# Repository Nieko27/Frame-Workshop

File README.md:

> ⚠️ This is an unofficial 3rd-party project with no association to Valve.

# What is Frame Workshop?
Frame Workshop is intended to be an open-source bundle of different hardware peripherals built around (but not always exclusive to) the Steam Frame. The idea is to leverage the Steam Frames' modularity and general openness to create a collection of open-source hardware projects that the community can provide feedback on, expand upon, or even take and turn into something entirely new, creating a feedback loop that adds to an ever-expanding ecosystem for the Steam Frame. All source files, from schematics to STLs, will be included, allowing every aspect of each project to be modified and produced to anyone’s preferences. 

## Hardware
Below is a list of all currently in development hardware projects, including a brief overview and notes on changes made to the most recent revision.

### Frame Facetracker

| 🛑R&D | hw: EV2 | 
| -------- | ------- |

The Frame face tracker is pretty self-explanatory: it is a module that uses a camera for face tracking in social experiences like VRChat. There are 2 versions planned: one built with the steam frame in mind, using its expansion ports, and another that plugs into the back USB port of the frame and uses an ESP32 to run the camera.

>Headset-Agnostic Version EV2

<br>

Link to the facetracker files:
[Here](https://github.com/Nieko27/FrameWork/tree/main/KICAD%20Projects/Primis_FaceTracker)

### Versipellis (General Purpose Dongle)

| 🟠WIP | hw: EV2 | 
| -------- | ------- |

Versipellis is a dongle utilising an nRF52833 intended as a general-purpose dongle for communicating with any Frame-based hardware, whether it be controllers or trackers. It will be programmable by the end user for whatever they intend to use it for. There will be two versions: one utilising no parts smaller than a 0603 package, making it easy to hand-assemble, and another using much smaller parts that, while smaller, will require assembly by a service like JLCPCB.

>Hand-assemblable EV1

<br>

Link to Versipellis' files:
[Here](https://github.com/Nieko27/FrameWork/tree/main/KICAD%20Projects/Primis_Versipellis)

### VeriMini

| 🛑R&D | hw: EV1 | 
| -------- | ------- |

Link to VeriMini files:
[Here](https://github.com/Nieko27/Frame-Workshop/tree/main/KICAD%20Projects/Primis_VeriMini)

### Locus (Tracker)

| 🛑R&D | hw: EV2 | 
| -------- | ------- |

Locus is intended to be a tracker like Vive or Tundra, but without reliance on lighthouse base stations. Since the Steam Frame isn’t limited to base station vision, trackers being used with it shouldn’t be either. Similar to Versipellis, Locus will also use an nRF52833 along with an LSM6DSV16X IMU. The idea is that it will track similarly to a slime tracker, but also use the Steam Frame’s optical tracking to address the drift problem of EMF trackers. 

Link to Locus' files:
[Here](https://github.com/Nieko27/FrameWork/tree/main/KICAD%20Projects/Primis_Locus)

## Project Status Indicator

| 🔵STATUS | hw: EV1 | fw: v0.0.0 | sw: v0.0.0 |
| -------- | ------- | ---------- | ---------- |

The above status indicator is listed for each Frame Workshop accessory. It shows overall progress as well as the latest upstreamed hardware, firmware, and/or software versions. Here's what each status means:

**🔴R&D**: This accessory is experimental. The latest hardware revision is either untested, incomplete, or broken. Capabilities are unproven. Form factor and design requirements may change entirely. Intended for use by hardware contributors.

**🟠WIP**: The current hardware revision has been tested and is fully capable of meeting established design requirements. Firmware and/or software are in active development. Future hardware revisions may still follow if oversights or improvements are discovered. Intended for use by software contributors.

**🟡PRE**: This accessory has reached a pre-release stage. Hardware is finalized. Firmware and software meets functional requirements but may still be buggy or unintuitive. Documentation is not yet up to release standards. Considered usable for tinkerers and early adopters.

**🟢REL**: This accessory is considered released and fully functional both in software and hardware. Documentation is available to assist with ordering components, assembly, and usage. Software and firmware QOL updates may still follow but will be distributed through user friendly means.

### Future Projects
* USB Hub
* Index speaker mod kit

## Accessories and CAD
While 3D models for each electronics project are in the 3D models folder, I also plan to make several other CAD files available for accessories that don't require electronics. Things like lens caps, headset stands, battery or IO expansion holders, etc.
<br>
https://github.com/Nieko27/Frame-Workshop/tree/main/3D%20Models/Accessories

## Project Goals

* Keep costs to the users as low as possible. You've already spent over a $1000 on the headset itself, so it would be nice not to have to spend another $1000 customizing it to your liking. How this would be achieved is by everything being open and nothing being sold, for example I’m working on a face tracker that takes advantage of the PCIe port on the Frame, the idea is when its done instead of me having to handle production, shipping and all the joys of selling a project I give the source files out with a tutorial on how to order it yourself from a company like JLCPCB. Now, obviously, this still won't be free to the end user, but it will be much cheaper than if I were to sell it. For example, I have made the first prototype of the face-tracker, and in small quantities (5 to be exact), it cost me $25 per board. Compare that to something like the old Vive face trackers, which I think were closer to $100, and you save a nice bit of money. 

* Give the end user total control over the hardware. Don't like how I've done something? Fire up Blender or KiCad and change it yourself to fit whatever need you have in mind. I know not everyone will be able to do this, as it requires familiarity with the software, but it gives people the ability to do so. Obviously, with this in mind, I want to make the experience for everyone as smooth as possible out of the box, so I will be listening to feedback as much as possible to achieve that. 

* Create a feedback loop. I have all this under a CERN-OHL-S-2.0 license, which (as far as I understand) means you can do anything you want with anything in the repo, including selling it for profit, but you must open-source anything you do under the same license. This way it keeps everything open to the community, and every addition helps grow the ecosystem around the Steam Frame. 

## Note
A forewarning, I am very new to electronics design in general. I apologize in advance for any really baffling design decisions. I hope to learn from these projects and will keep them updated as I learn more. Thank you for your patience.

## Ideas
A few ideas for possible mods for the Frame have already been thrown around. If you have an idea for a mod, whether it's a full module or as simple as a 3D-printable counterweight, feel free to open a pull request under the enhancement tag. You may also feel free to email me at nieko972@gmail.com.

### Find me on
* Twitter; https://x.com/Merlinr271
* Bluesky; https://bsky.app/profile/merlin271.bsky.social

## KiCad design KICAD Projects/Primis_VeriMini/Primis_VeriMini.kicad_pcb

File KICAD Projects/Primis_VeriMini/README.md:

### Status

| 🛑R&D | hw: EV1 | 
| -------- | ------- |

> This accessory is experimental. The latest hardware revision is either untested, incomplete, or broken. Capabilities are unproven. Form factor and design requirements may change entirely. Intended for use by hardware contributors.

# VERI-MINI
The general purpose dongle for the Steam Frame but smaller.

### Schematics

### PCB

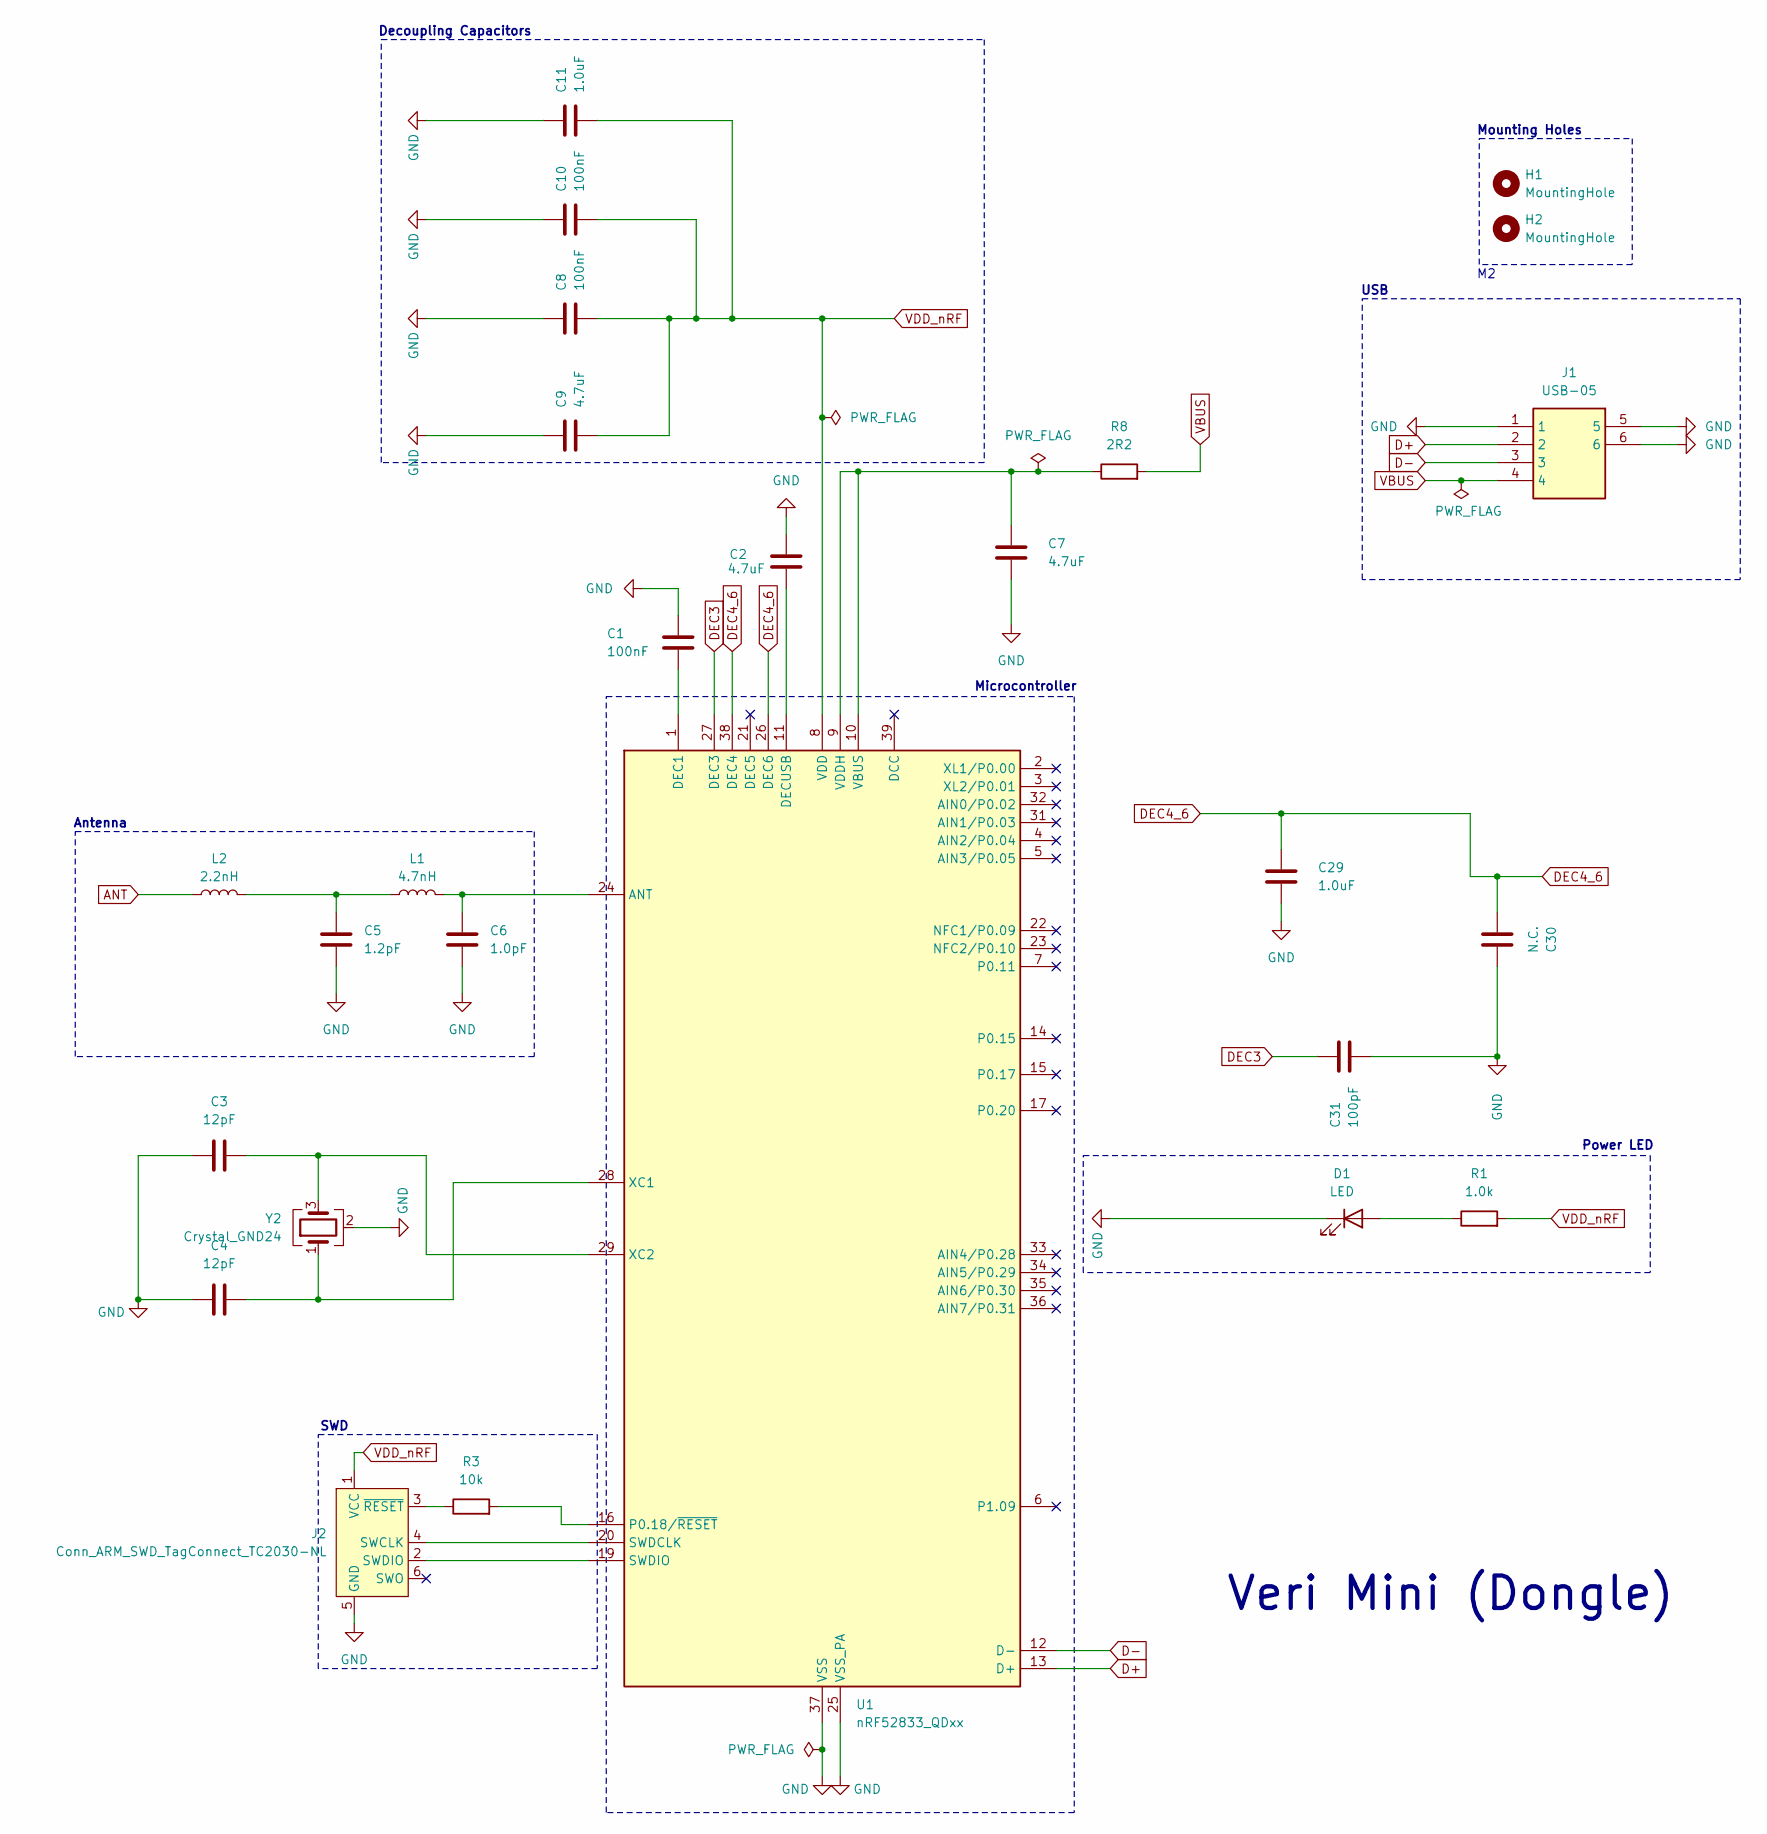
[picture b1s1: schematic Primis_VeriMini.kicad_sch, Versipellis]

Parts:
C1, C8, C10: 100nF; C_0402_1005Metric
C2, C7, C9: 4.7uF; C_0603_1608Metric
C3, C4: 12pF; C_0402_1005Metric
C5: 1.2pF; C_0402_1005Metric
C6: 1.0pF; C_0402_1005Metric
C11, C29: 1.0uF; C_0402_1005Metric
C30: N.C.; C_0402_1005Metric
C31: 100pF; C_0402_1005Metric
D1: LED; LED_0603_1608Metric
H1, H2: MountingHole; MountingHole_2.2mm_M2
J1: USB-05; USB05; Manufacturer_Part_Number USB-05
J2: Conn_ARM_SWD_TagConnect_TC2030-NL; Tag-Connect_TC2030-IDC-NL_2x03_P1.27mm_Vertical
L1: 4.7nH; L_0402_1005Metric
L2: 2.2nH; L_0402_1005Metric
R1: 1.0k; R_0402_1005Metric
R3: 10k; R_0603_1608Metric
R8: 2R2; R_0603_1608Metric
U1: nRF52833_QDxx; QFN-40-1EP_5x5mm_P0.4mm_EP3.6x3.6mm
Y2: Crystal_GND24; Crystal_SMD_Abracon_ABM8G-4Pin_3.2x2.5mm

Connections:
ANT: L2.1
D+: J1.2, U1.13 (D+)
D-: J1.3, U1.12 (D-)
DEC3: C31.1, U1.27 (DEC3)
DEC4_6: C29.1, C30.2, U1.26 (DEC6), U1.38 (DEC4)
GND: C1.1, C2.2, C3.1, C4.1, C5.1, C6.1, C7.2, C8.1, C9.2, C10.1, C11.2, C29.2, C30.1, C31.2, D1.1 (K), J1.1, J1.5, J1.6, J2.5 (GND), U1.25 (VSS_PA), U1.37 (VSS), U1.41 (VSS), Y2.2 (G), Y2.4 (G)
unnamed: C5.2, L1.1, L2.2
unnamed: D1.2 (A), R1.1
unnamed: J2.4 (SWCLK), U1.20 (SWDCLK)
unnamed: J2.2 (SWDIO), U1.19 (SWDIO)
unnamed: J2.3 (~RESET), R3.1
unnamed: C6.2, L1.2, U1.24 (ANT)
unnamed: C1.2, U1.1 (DEC1)
unnamed: C2.1, U1.11 (DECUSB)
unnamed: R3.2, U1.16 (P0.18/~RESET)
unnamed: C7.1, R8.1, U1.9 (VDDH), U1.10 (VBUS)
unnamed: C4.2, U1.28 (XC1), Y2.1
unnamed: C3.2, U1.29 (XC2), Y2.3
VBUS: J1.4, R8.2
VDD_nRF: C8.2, C9.1, C10.2, C11.1, J2.1 (VCC), R1.2, U1.8 (VDD), U1.18 (VDD), U1.30 (VDD), U1.40 (VDD)

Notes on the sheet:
Mounting Holes
Decoupling Capacitors
Microcontroller
Veri Mini (Dongle)
SWD
Antenna
Power LED
USB

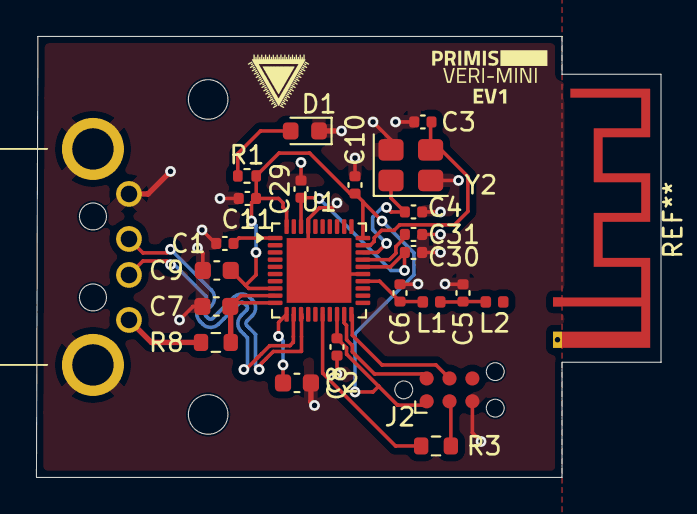
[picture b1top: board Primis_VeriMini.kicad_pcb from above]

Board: 2 copper layers, 34.7 x 24.5 mm, 26 parts (0 on the bottom side), 19 nets.

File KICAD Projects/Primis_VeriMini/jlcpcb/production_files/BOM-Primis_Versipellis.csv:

Comment,Designator,Footprint,LCSC,Quantity
1.2pF,C5,C_0603_1608Metric,,1
2R2,R8,R_0805_2012Metric,,1
1.0pF,C6,C_0603_1608Metric,,1
12pF,C4,C_0603_1608Metric,,1
4.7uF,C2,C_0603_1608Metric,,1
USB-05,J1,USB05,,1
WS2812B-2020,D3,LED_WS2812B-2020_PLCC4_2.0x2.0mm,,1
4.7uF,C9,C_0603_1608Metric,,1
nRF52833_QDxx,U1,QFN-40-1EP_5x5mm_P0.4mm_EP3.6x3.6mm,,1
100nF,C8,C_0603_1608Metric,,1
12pF,C3,C_0603_1608Metric,,1
100pF,C31,C_0603_1608Metric,,1
1.0k,R1,R_0603_1608Metric,,1
4.7uF,C7,C_0603_1608Metric,,1
LED,D1,LED_0603_1608Metric,,1
N.C.,C30,C_0603_1608Metric,,1
1.0uF,C29,C_0603_1608Metric,,1
1.0uF,C11,C_0603_1608Metric,,1
Crystal_GND24,Y2,Crystal_SMD_Abracon_ABM8G-4Pin_3.2x2.5mm,,1
100nF,C10,C_0603_1608Metric,,1
2.2nH,L2,L_0603_1608Metric,,1
10k,R3,R_0603_1608Metric,,1
4.7nH,L1,L_0603_1608Metric,,1
100nF,C1,C_0603_1608Metric,,1
100nF,C12,C_0603_1608Metric,,1

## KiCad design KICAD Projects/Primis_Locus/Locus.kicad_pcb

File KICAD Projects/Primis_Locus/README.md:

### Status

| 🛑R&D | hw: EV2 | 
| -------- | ------- |

> This accessory is experimental. The latest hardware revision is either untested, incomplete, or broken. Capabilities are unproven. Form factor and design requirements may change entirely. Intended for use by hardware contributors.

## Current Isseus
Currently the SDA line is getting pulled 0.02v while running the slime firmware, if I halt the NRF52833 it jumps up to the expected 1.8v. Currently working on figuring out why this happens.

### Schematics

### PCB

### EV1

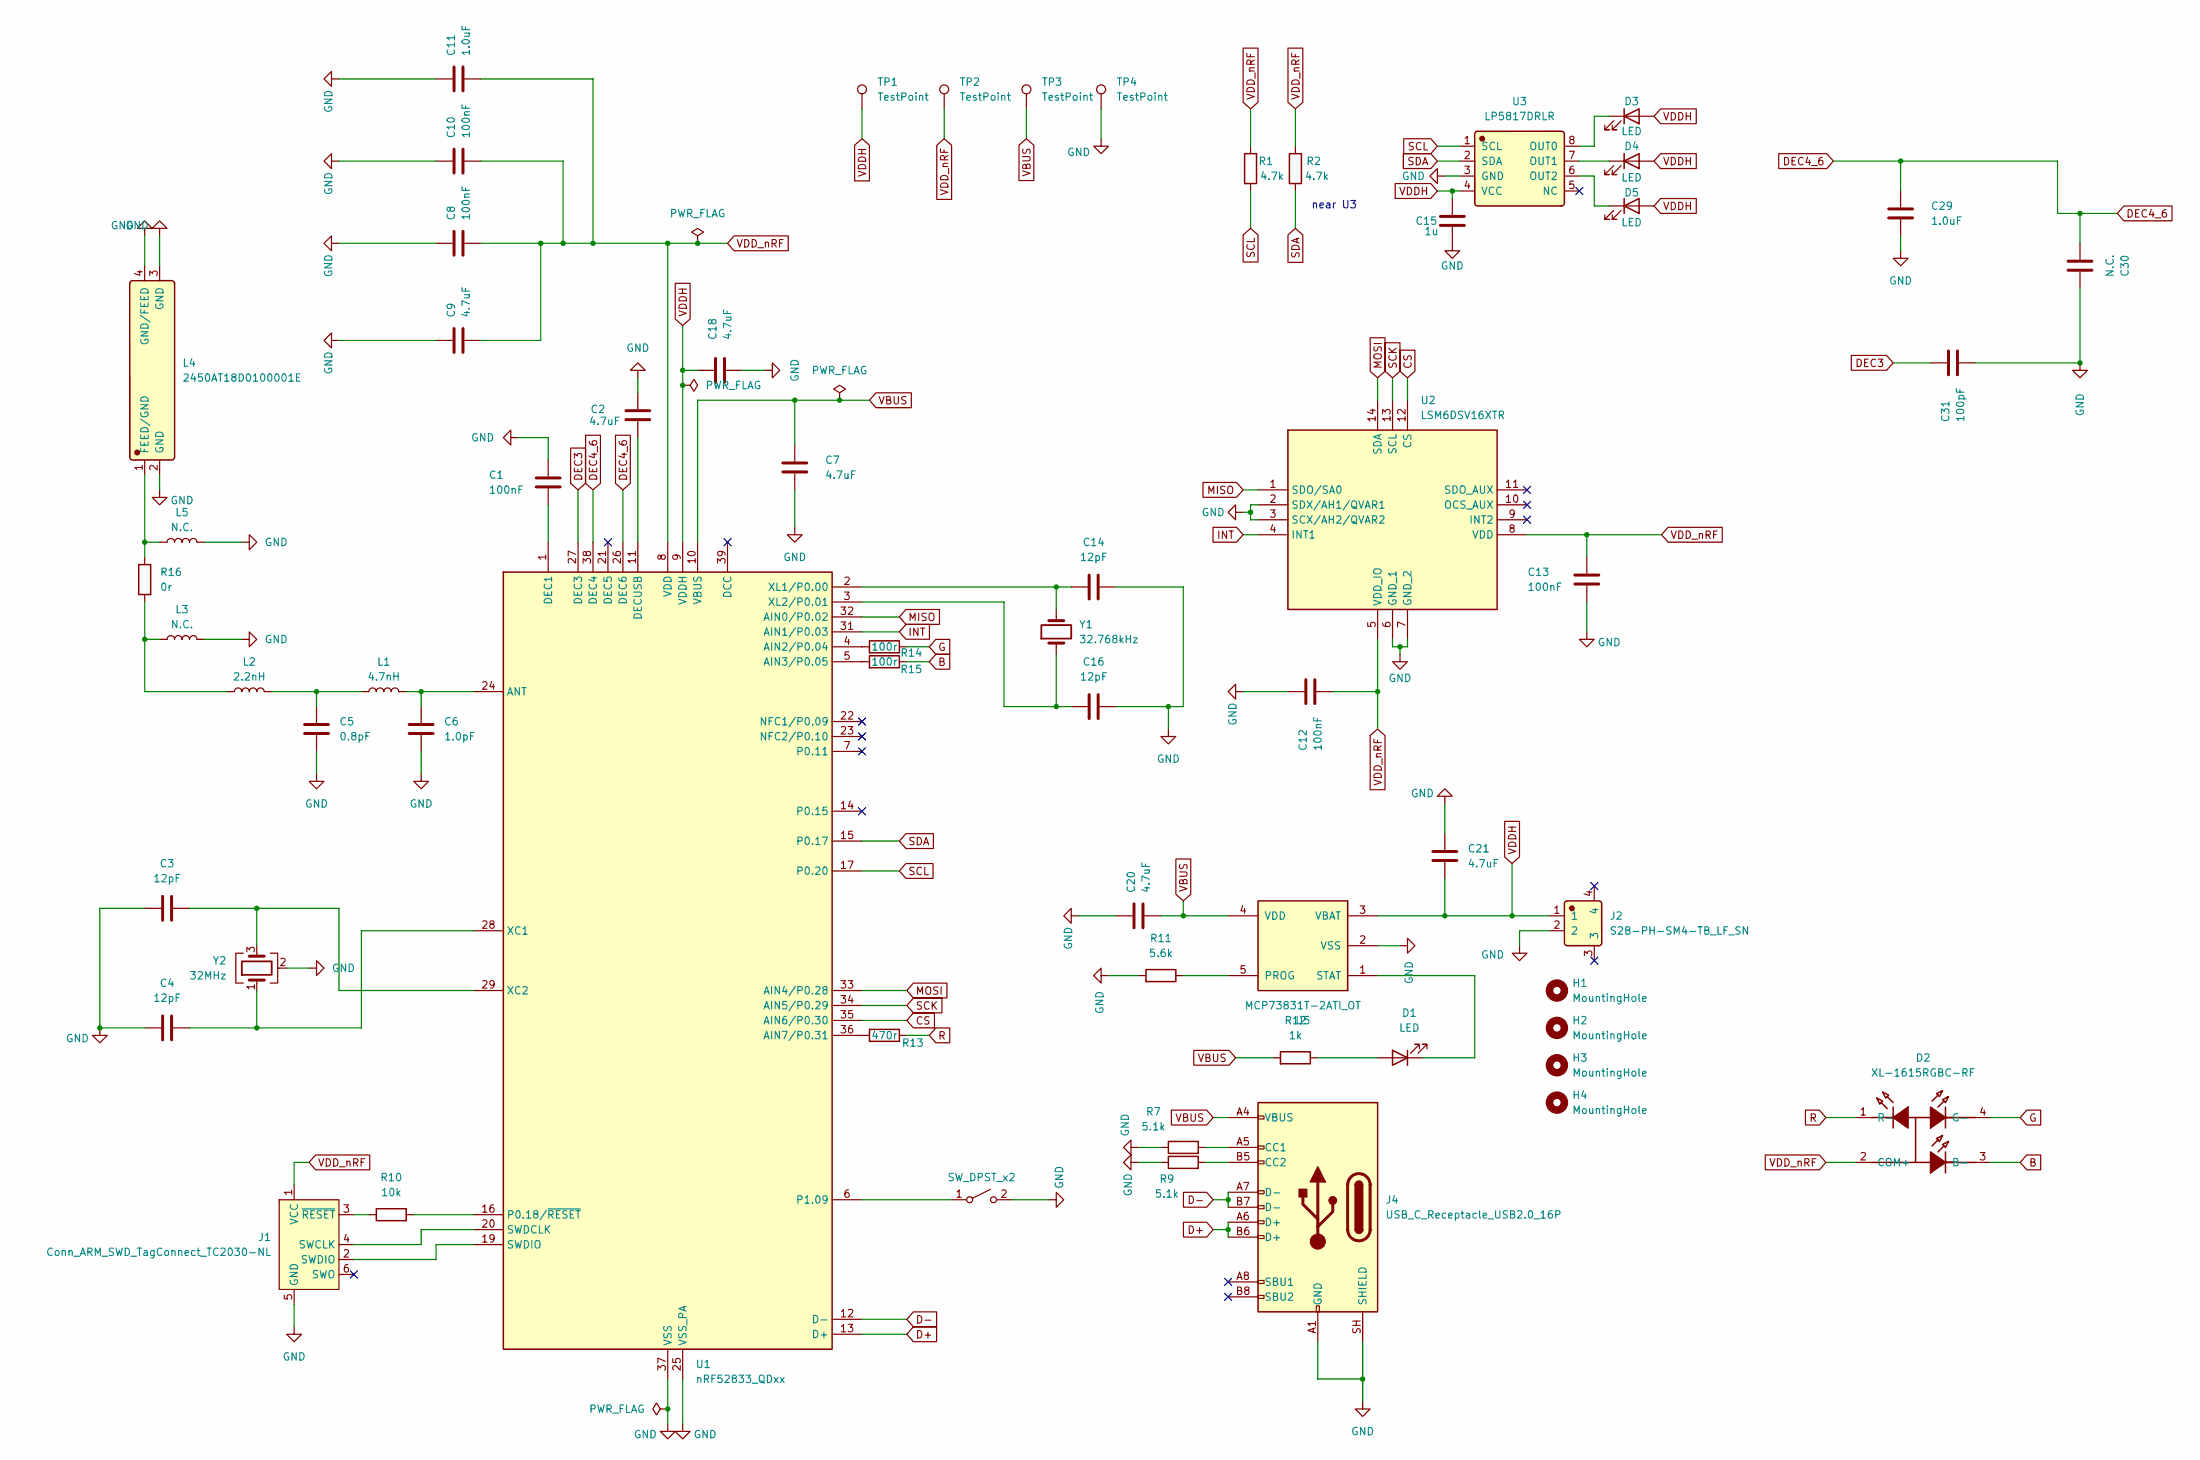
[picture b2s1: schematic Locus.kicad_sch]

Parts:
C1, C8, C10, C12, C13: 100nF; C_0402_1005Metric
C2, C7, C9, C18, C20, C21: 4.7uF; C_0603_1608Metric
C3, C4, C14, C16: 12pF; C_0402_1005Metric
C5: 0.8pF; C_0402_1005Metric
C6: 1.0pF; C_0402_1005Metric
C11, C29: 1.0uF; C_0402_1005Metric
C15: 1u; C_0402_1005Metric
C30: N.C.; C_0402_1005Metric
C31: 100pF; C_0402_1005Metric
D1: LED; LED_0603_1608Metric
D2: XL-1615RGBC-RF; Manufacturer Part XL-1615RGBC-RF; LCSC C965840
D3, D4, D5: LED; LED_0805_2012Metric
H1, H2, H3, H4: MountingHole; MountingHole_2.7mm_M2.5
J1: Conn_ARM_SWD_TagConnect_TC2030-NL; Tag-Connect_TC2030-IDC-NL_2x03_P1.27mm_Vertical
J2: S2B-PH-SM4-TB_LF_SN; Manufacturer Part S2B-PH-SM4-TB(LF)(SN); LCSC C295747
J4: USB_C_Receptacle_USB2.0_16P; USB_C_Receptacle_HRO_TYPE-C-31-M-12
L1: 4.7nH; L_0402_1005Metric
L2: 2.2nH; L_0402_1005Metric
L3, L5: N.C.; L_0402_1005Metric
L4: 2450AT18D0100001E; Manufacturer Part 2450AT18D0100001E; LCSC C7450310
R1, R2: 4.7k; R_0402_1005Metric
R7, R9: 5.1k; R_0402_1005Metric
R10: 10k; R_0402_1005Metric
R11: 5.6k; R_0402_1005Metric
R12: 1k; R_0402_1005Metric
R13: 470r; R_0402_1005Metric
R14, R15: 100r; R_0402_1005Metric
R16: 0r; R_0402_1005Metric
SW1: SW_DPST_x2; SH-1806SA-A3DW-04
TP1, TP2, TP3, TP4: TestPoint; TestPoint_Pad_1.0x1.0mm
U1: nRF52833_QDxx; QFN-40-1EP_5x5mm_P0.4mm_EP3.6x3.6mm
U2: LSM6DSV16XTR; LSM6DSV16BXTR; Manufacturer_Part_Number LSM6DSV16XTR; Mouser Part Number 511-LSM6DSV16XTR
U3: LP5817DRLR; Manufacturer Part LP5817DRLR; LCSC C47262829
U5: MCP73831T-2ATI_OT; Manufacturer Part MCP73831T-2ATI/OT; LCSC C14879
Y1: 32.768kHz; SC-20S32_768kHz20PPM9pF
Y2: 32MHz; NX2016SA-32MHZ-STD-CZS-5

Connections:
B: D2.3 (B-), R15.1
CS: U1.35 (AIN6/P0.30), U2.12 (CS)
D+: J4.A6 (D+), J4.B6 (D+), U1.13 (D+)
D-: J4.A7 (D-), J4.B7 (D-), U1.12 (D-)
DEC3: C31.1, U1.27 (DEC3)
DEC4_6: C29.1, C30.2, U1.26 (DEC6), U1.38 (DEC4)
G: D2.4 (G-), R14.1
GND: C1.1, C2.2, C3.1, C4.1, C5.1, C6.1, C7.2, C8.1, C9.2, C10.1, C11.2, C12.1, C13.2, C14.1, C15.2, C16.2, C18.2, C20.2, C21.1, C29.2, C30.1, C31.2, J1.5 (GND), J2.2, J4.A1 (GND), J4.A12 (GND), J4.B1 (GND), J4.B12 (GND), J4.SH (SHIELD), L3.2, L4.2 (GND), L4.3 (GND), L4.4 (GND/FEED), L5.2, R7.1, R9.1, R11.2, SW1.2 (B), TP4.1 (1_1), U1.25 (VSS_PA), U1.37 (VSS), U1.41 (VSS), U2.2 (SDX/AH1/QVAR1), U2.3 (SCX/AH2/QVAR2), U2.6 (GND_1), U2.7 (GND_2), U3.3 (GND), U5.2 (VSS), Y2.2 (G), Y2.4 (G)
INT: U1.31 (AIN1/P0.03), U2.4 (INT1)
MISO: U1.32 (AIN0/P0.02), U2.1 (SDO/SA0)
MOSI: U1.33 (AIN4/P0.28), U2.14 (SDA)
unnamed: C5.2, L1.1, L2.2
unnamed: D1.2 (A), R12.1
unnamed: D1.1 (K), U5.1 (STAT)
unnamed: D3.1 (K), U3.8 (OUT0)
unnamed: D4.1 (K), U3.7 (OUT1)
unnamed: D5.1 (K), U3.6 (OUT2)
unnamed: J1.4 (SWCLK), U1.20 (SWDCLK)
unnamed: J1.2 (SWDIO), U1.19 (SWDIO)
unnamed: J1.3 (~RESET), R10.1
unnamed: J4.A5 (CC1), R7.2
unnamed: J4.B5 (CC2), R9.2
unnamed: L2.1, L3.1, R16.2
unnamed: L4.1 (FEED/GND), L5.1, R16.1
unnamed: SW1.1 (A), U1.6 (P1.09)
unnamed: R14.2, U1.4 (AIN2/P0.04)
unnamed: R15.2, U1.5 (AIN3/P0.05)
unnamed: R13.2, U1.36 (AIN7/P0.31)
unnamed: C6.2, L1.2, U1.24 (ANT)
unnamed: C1.2, U1.1 (DEC1)
unnamed: C2.1, U1.11 (DECUSB)
unnamed: R10.2, U1.16 (P0.18/~RESET)
unnamed: C4.2, U1.28 (XC1), Y2.1
unnamed: C3.2, U1.29 (XC2), Y2.3
unnamed: C14.2, U1.2 (XL1/P0.00), Y1.2
unnamed: C16.1, U1.3 (XL2/P0.01), Y1.1
unnamed: R11.1, U5.5 (PROG)
R: D2.1 (R-), R13.1
SCK: U1.34 (AIN5/P0.29), U2.13 (SCL)
SCL: R1.2, U1.17 (P0.20), U3.1 (SCL)
SDA: R2.2, U1.15 (P0.17), U3.2 (SDA)
VBUS: C7.1, C20.1, J4.A4 (VBUS), J4.A9 (VBUS), J4.B4 (VBUS), J4.B9 (VBUS), R12.2, TP3.1 (1_1), U1.10 (VBUS), U5.4 (VDD)
VDDH: C15.1, C18.1, C21.2, D3.2 (A), D4.2 (A), D5.2 (A), J2.1, TP1.1 (1_1), U1.9 (VDDH), U3.4 (VCC), U5.3 (VBAT)
VDD_nRF: C8.2, C9.1, C10.2, C11.1, C12.2, C13.1, D2.2 (COM+), J1.1 (VCC), R1.1, R2.1, TP2.1 (1_1), U1.8 (VDD), U1.18 (VDD), U1.30 (VDD), U1.40 (VDD), U2.5 (VDD_IO), U2.8 (VDD)

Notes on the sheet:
near U3

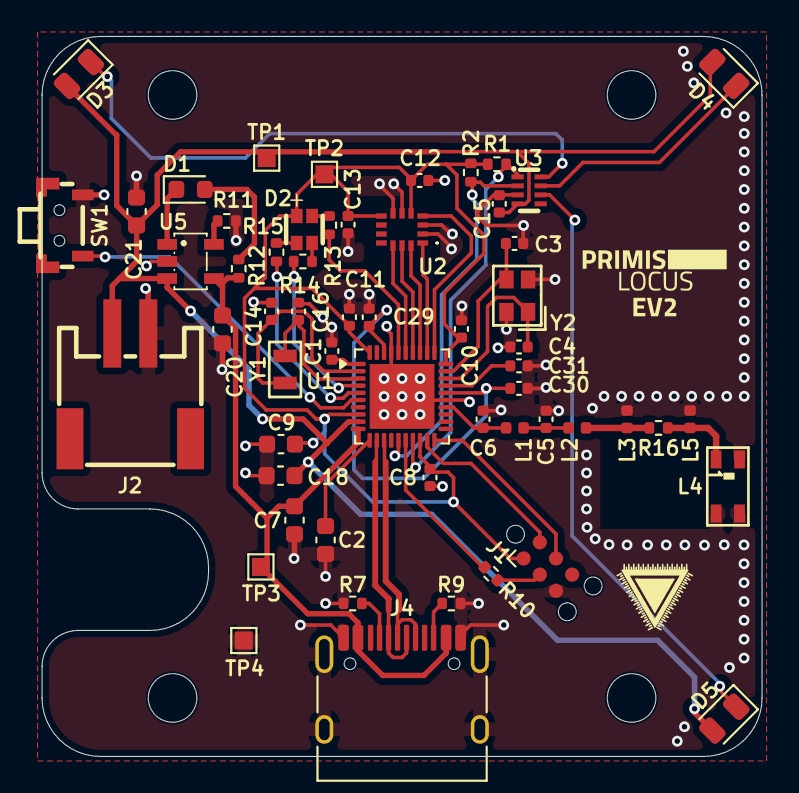
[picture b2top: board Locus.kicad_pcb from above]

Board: 4 copper layers, 40.0 x 40.0 mm, 61 parts (0 on the bottom side), 44 nets.

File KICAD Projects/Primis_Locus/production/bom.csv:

Designator,Footprint,Quantity,Value,LCSC Part #
"C1, C10, C12, C13, C8",0402,5,100nF,
"C11, C29",0402,2,1.0uF,
"C14, C16, C3, C4",0402,4,12pF,
C17,0603,1,2.2uF,
"C18, C2, C20, C21, C7, C9",0603,6,4.7uF,
"C30, L3, L5",0402,3,N.C.,
C31,0402,1,100pF,
C5,0402,1,0.8pF,
C6,0402,1,1.0pF,
D1,0603,1,LED,
D2,XL-1615RGBC-RF,1,XL-1615RGBC-RF,C965840
J2,S2B-PH-SM4-TB_LF_SN,1,S2B-PH-SM4-TB_LF_SN,C295747
J4,USB_C_Receptacle_HRO_TYPE-C-31-M-12,1,USB_C_Receptacle_USB2.0_16P,
L1,0402,1,4.7nH,
L2,0402,1,2.2nH,
L4,2450AT18D0100001E,1,2450AT18D0100001E,C7450310
"R1, R2, R4",0402,3,4.7k,
R10,0402,1,10k,
R11,0402,1,5.6k,
R12,0402,1,1k,
R13,0402,1,470r,
"R14, R15",0402,2,100r,
R16,0402,1,0r,
"R7, R9",0402,2,5.1k,
SW1,SH-1806SA-A3DW-04,1,SW_DPST_x2,C22383476
"TP1, TP2, TP3, TP4",TestPoint_Pad_1.0x1.0mm,4,TestPoint,
U1,QFN-40-1EP_5x5mm_P0.4mm_EP3.6x3.6mm,1,nRF52833_QDxx,
U2,LSM6DSV16BXTR,1,LSM6DSV16XTR,
U3,QMC6309,1,QMC6309,
U5,MCP73831T-2ATI_OT,1,MCP73831T-2ATI_OT,C14879
Y1,SC-20S32_768kHz20PPM9pF,1,32.768kHz,C97603
Y2,NX2016SA-32MHZ-STD-CZS-5,1,32MHz,C843260

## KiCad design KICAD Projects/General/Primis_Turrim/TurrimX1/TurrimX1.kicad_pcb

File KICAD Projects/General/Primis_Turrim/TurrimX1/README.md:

### WARNING
This has yet to be produced by me yet, I have not yet added the gerber files to this repo yet as I have no idea if it will work yet, order them at your own risk.
# Dongle Dock (1-Port)
Headset-agnostic face tracker. Can be used with Frame by using the USB-C port on the battery.

### Schematics

### PCB

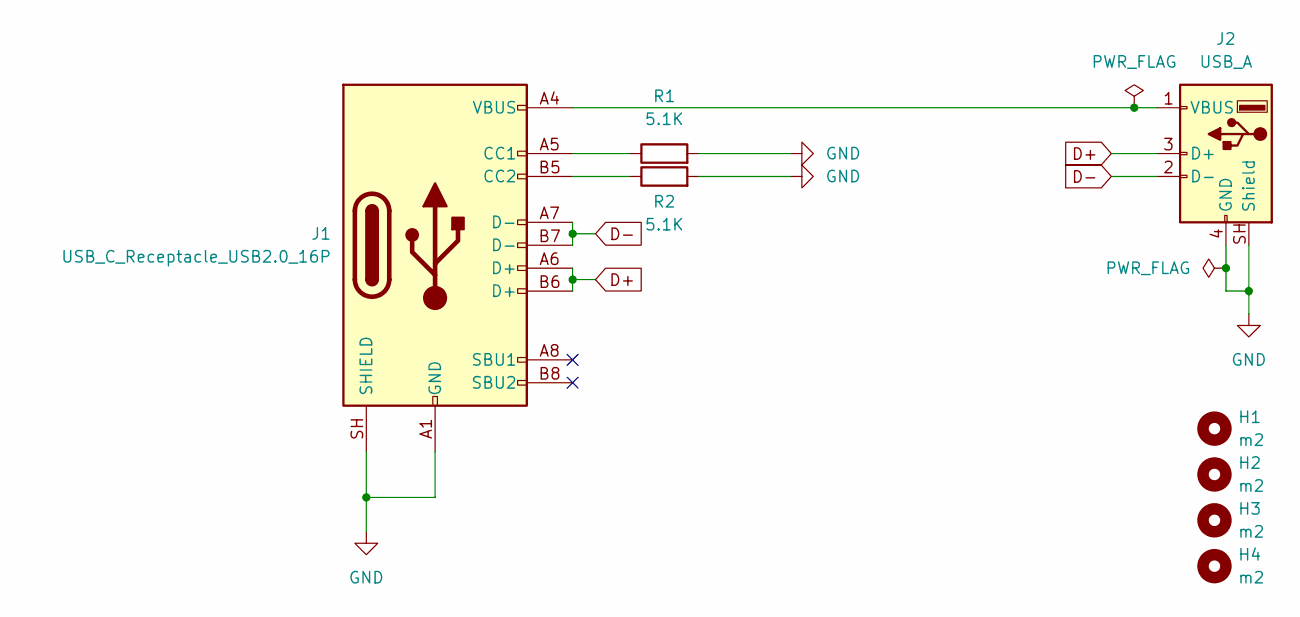
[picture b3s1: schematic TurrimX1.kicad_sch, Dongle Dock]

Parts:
H1, H2, H3, H4: m2; MountingHole_2.2mm_M2
J1: USB_C_Receptacle_USB2.0_16P; USB_C_Receptacle_HRO_TYPE-C-31-M-12
J2: USB_A; USB_A_Molex_105057_Vertical
R1, R2: 5.1K; R_0805_2012Metric

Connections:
D+: J1.A6 (D+), J1.B6 (D+), J2.3 (D+)
D-: J1.A7 (D-), J1.B7 (D-), J2.2 (D-)
GND: J1.A1 (GND), J1.A12 (GND), J1.B1 (GND), J1.B12 (GND), J1.SH (SHIELD), J2.4 (GND), J2.SH (Shield), R1.2, R2.2
unnamed: J1.A5 (CC1), R1.1
unnamed: J1.B5 (CC2), R2.1
unnamed: J1.A4 (VBUS), J1.A9 (VBUS), J1.B4 (VBUS), J1.B9 (VBUS), J2.1 (VBUS)

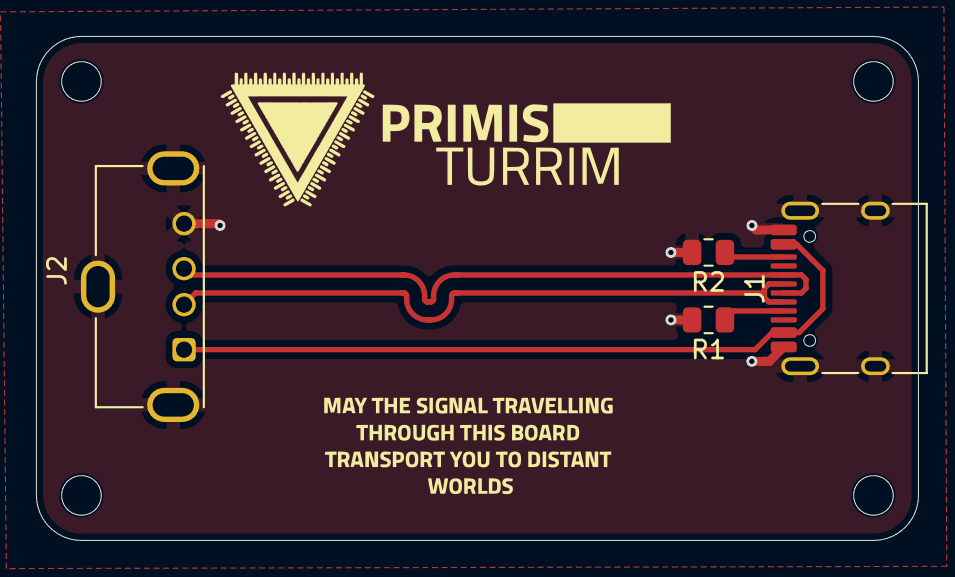
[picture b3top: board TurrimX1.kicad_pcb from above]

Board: 2 copper layers, 49.0 x 28.0 mm, 8 parts (0 on the bottom side), 6 nets.

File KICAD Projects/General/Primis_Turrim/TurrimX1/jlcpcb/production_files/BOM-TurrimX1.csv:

Comment,Designator,Footprint,LCSC,Quantity
5.1K,R2,R_0805_2012Metric,,1
5.1K,R1,R_0805_2012Metric,,1
USB_A,J2,USB_A_Molex_105057_Vertical,,1
USB_C_Receptacle_USB2.0_16P,J1,USB_C_Receptacle_HRO_TYPE-C-31-M-12,,1

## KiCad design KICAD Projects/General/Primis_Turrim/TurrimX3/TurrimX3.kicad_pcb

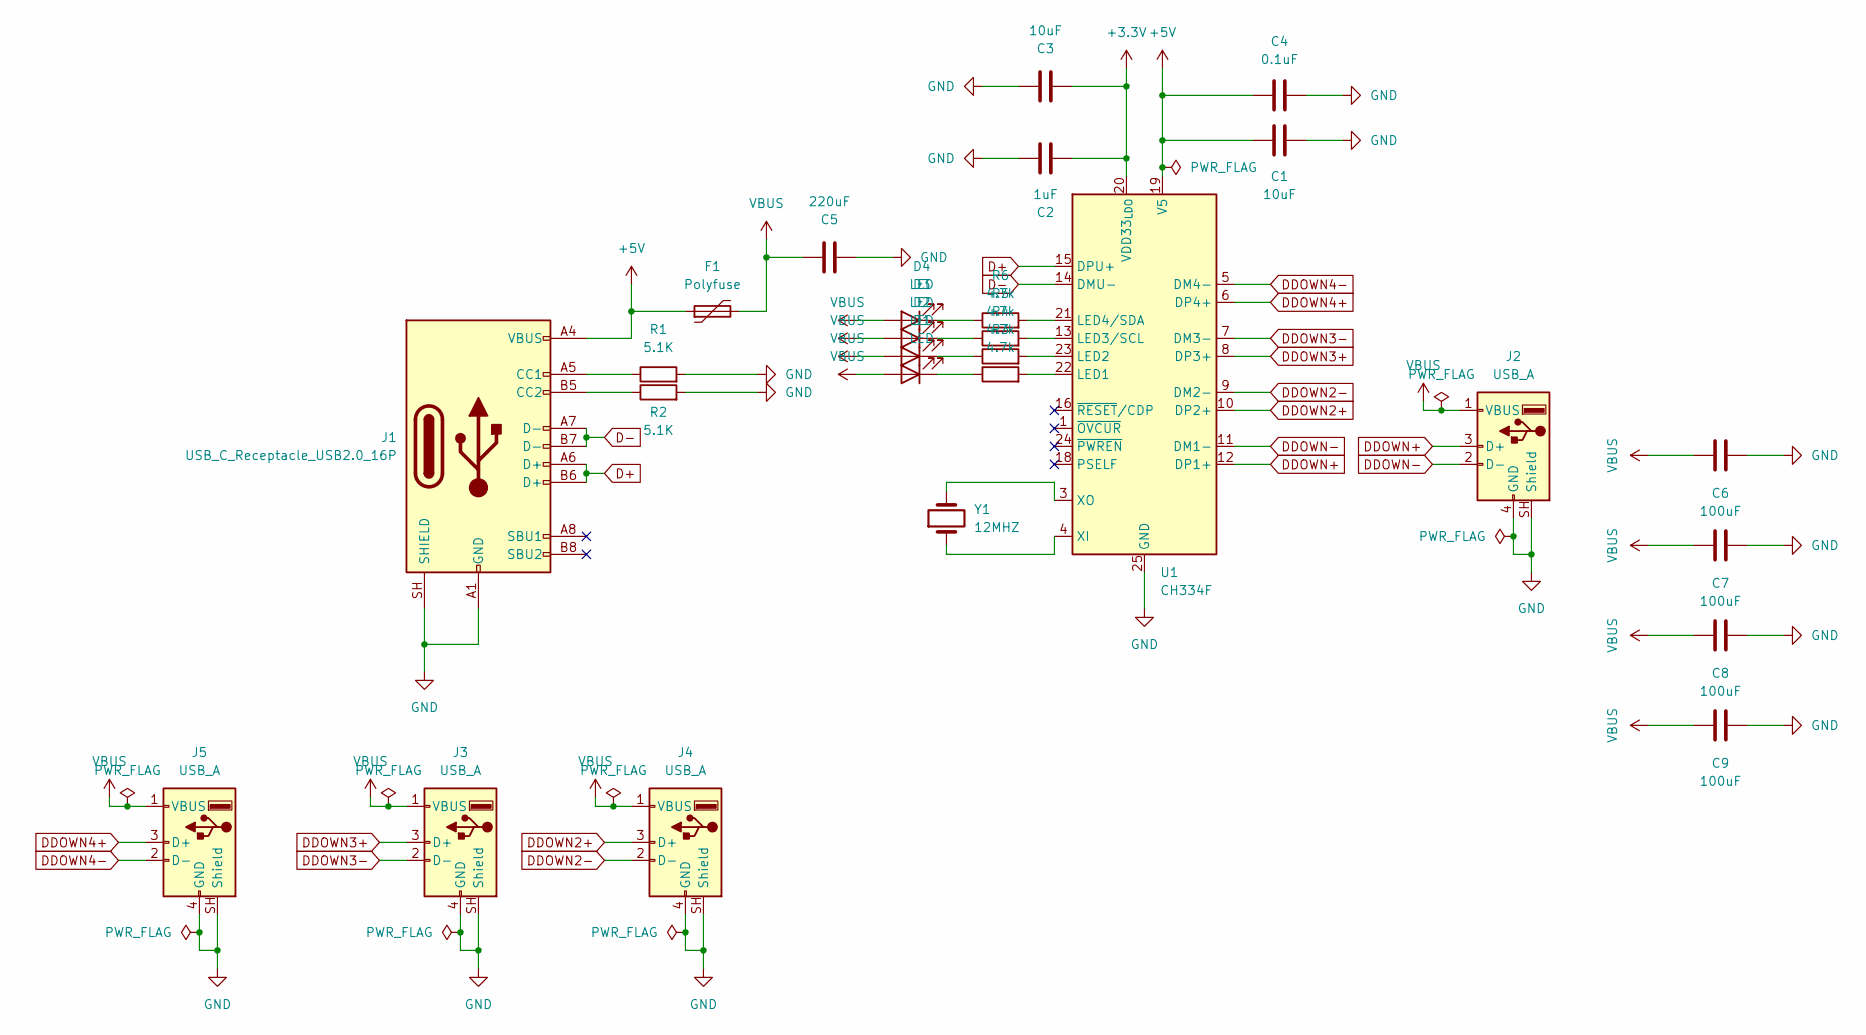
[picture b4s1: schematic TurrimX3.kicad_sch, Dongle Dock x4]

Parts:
C1, C3: 10uF; C_0805_2012Metric
C2: 1uF; C_0603_1608Metric
C4: 0.1uF; C_0603_1608Metric
C5: 220uF; C_0805_2012Metric
C6, C7, C8, C9: 100uF; C_0805_2012Metric
D1, D2, D3, D4: LED; LED_0603_1608Metric
F1: Polyfuse; Fuse_1206_3216Metric
J1: USB_C_Receptacle_USB2.0_16P; USB_C_Receptacle_HRO_TYPE-C-31-M-12
J2, J3, J4, J5: USB_A; USB_A_Molex_105057_Vertical
R1, R2: 5.1K; R_0805_2012Metric
R3, R4, R5, R6: 4.7k; R_0805_2012Metric
U1: CH334F; QFN-24-1EP_4x4mm_P0.5mm_EP2.7x2.7mm
Y1: 12MHZ; Crystal_SMD_2016-4Pin_2.0x1.6mm

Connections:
+3.3V: C2.1, C3.1, U1.20 (VDD33_{LDO})
+5V: C1.1, C4.1, F1.1, J1.A4 (VBUS), J1.A9 (VBUS), J1.B4 (VBUS), J1.B9 (VBUS), U1.19 (V5)
D+: J1.A6 (D+), J1.B6 (D+), U1.15 (DPU+)
D-: J1.A7 (D-), J1.B7 (D-), U1.14 (DMU-)
DDOWN2+: J4.3 (D+), U1.10 (DP2+)
DDOWN2-: J4.2 (D-), U1.9 (DM2-)
DDOWN3+: J3.3 (D+), U1.8 (DP3+)
DDOWN3-: J3.2 (D-), U1.7 (DM3-)
DDOWN4+: J5.3 (D+), U1.6 (DP4+)
DDOWN4-: J5.2 (D-), U1.5 (DM4-)
DDOWN+: J2.3 (D+), U1.12 (DP1+)
DDOWN-: J2.2 (D-), U1.11 (DM1-)
GND: C1.2, C2.2, C3.2, C4.2, C5.1, C6.2, C7.2, C8.2, C9.2, J1.A1 (GND), J1.A12 (GND), J1.B1 (GND), J1.B12 (GND), J1.SH (SHIELD), J2.4 (GND), J2.SH (Shield), J3.4 (GND), J3.SH (Shield), J4.4 (GND), J4.SH (Shield), J5.4 (GND), J5.SH (Shield), R1.2, R2.2, U1.25 (GND)
unnamed: D1.1 (K), R3.1
unnamed: D2.1 (K), R4.1
unnamed: D3.1 (K), R5.1
unnamed: D4.1 (K), R6.1
unnamed: J1.A5 (CC1), R1.1
unnamed: J1.B5 (CC2), R2.1
unnamed: R3.2, U1.22 (LED1)
unnamed: R4.2, U1.23 (LED2)
unnamed: R5.2, U1.13 (LED3/SCL)
unnamed: R6.2, U1.21 (LED4/SDA)
unnamed: U1.4 (XI), Y1.1
unnamed: U1.3 (XO), Y1.2
VBUS: C5.2, C6.1, C7.1, C8.1, C9.1, D1.2 (A), D2.2 (A), D3.2 (A), D4.2 (A), F1.2, J2.1 (VBUS), J3.1 (VBUS), J4.1 (VBUS), J5.1 (VBUS)

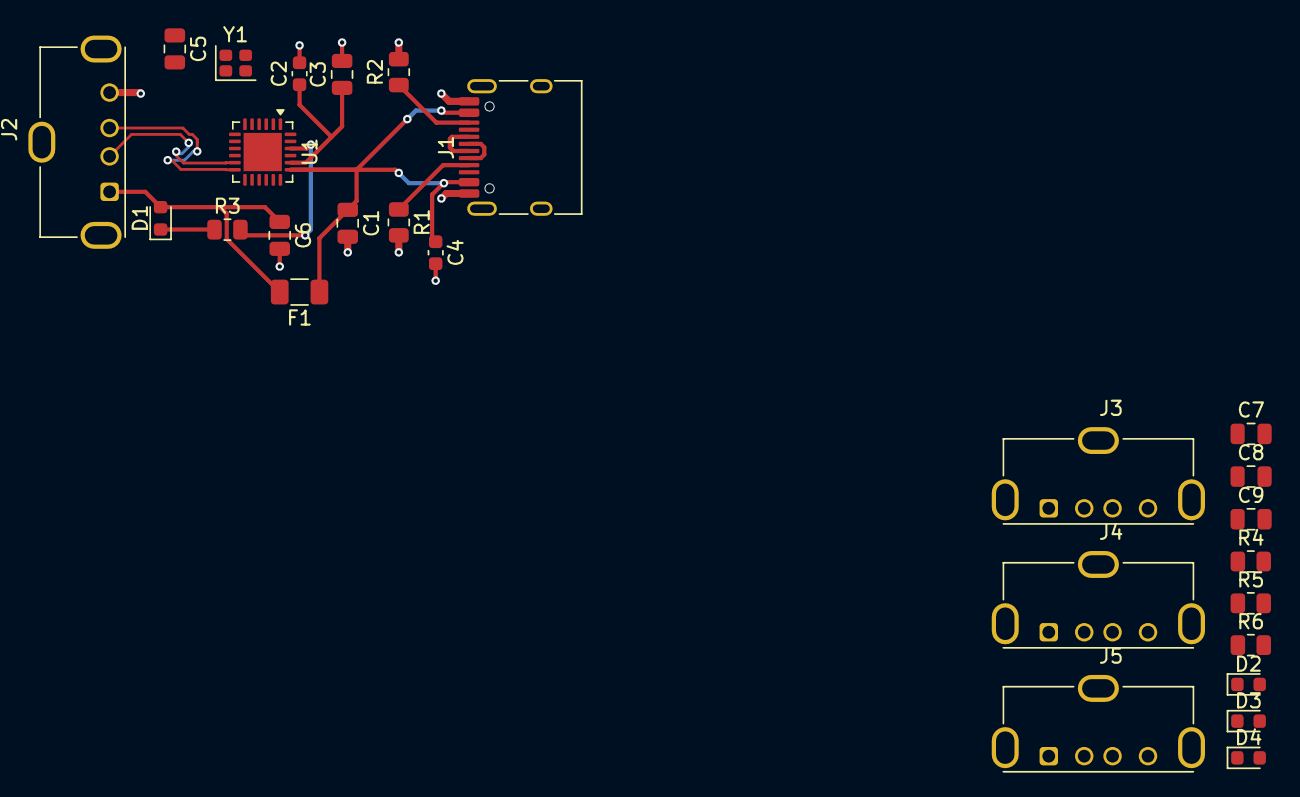
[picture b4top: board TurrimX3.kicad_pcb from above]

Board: 2 copper layers, 27 parts (0 on the bottom side), 26 nets.
